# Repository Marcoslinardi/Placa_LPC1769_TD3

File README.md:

# Placa_LPC1769_TD3
Placa de desarrollo para LPC1769

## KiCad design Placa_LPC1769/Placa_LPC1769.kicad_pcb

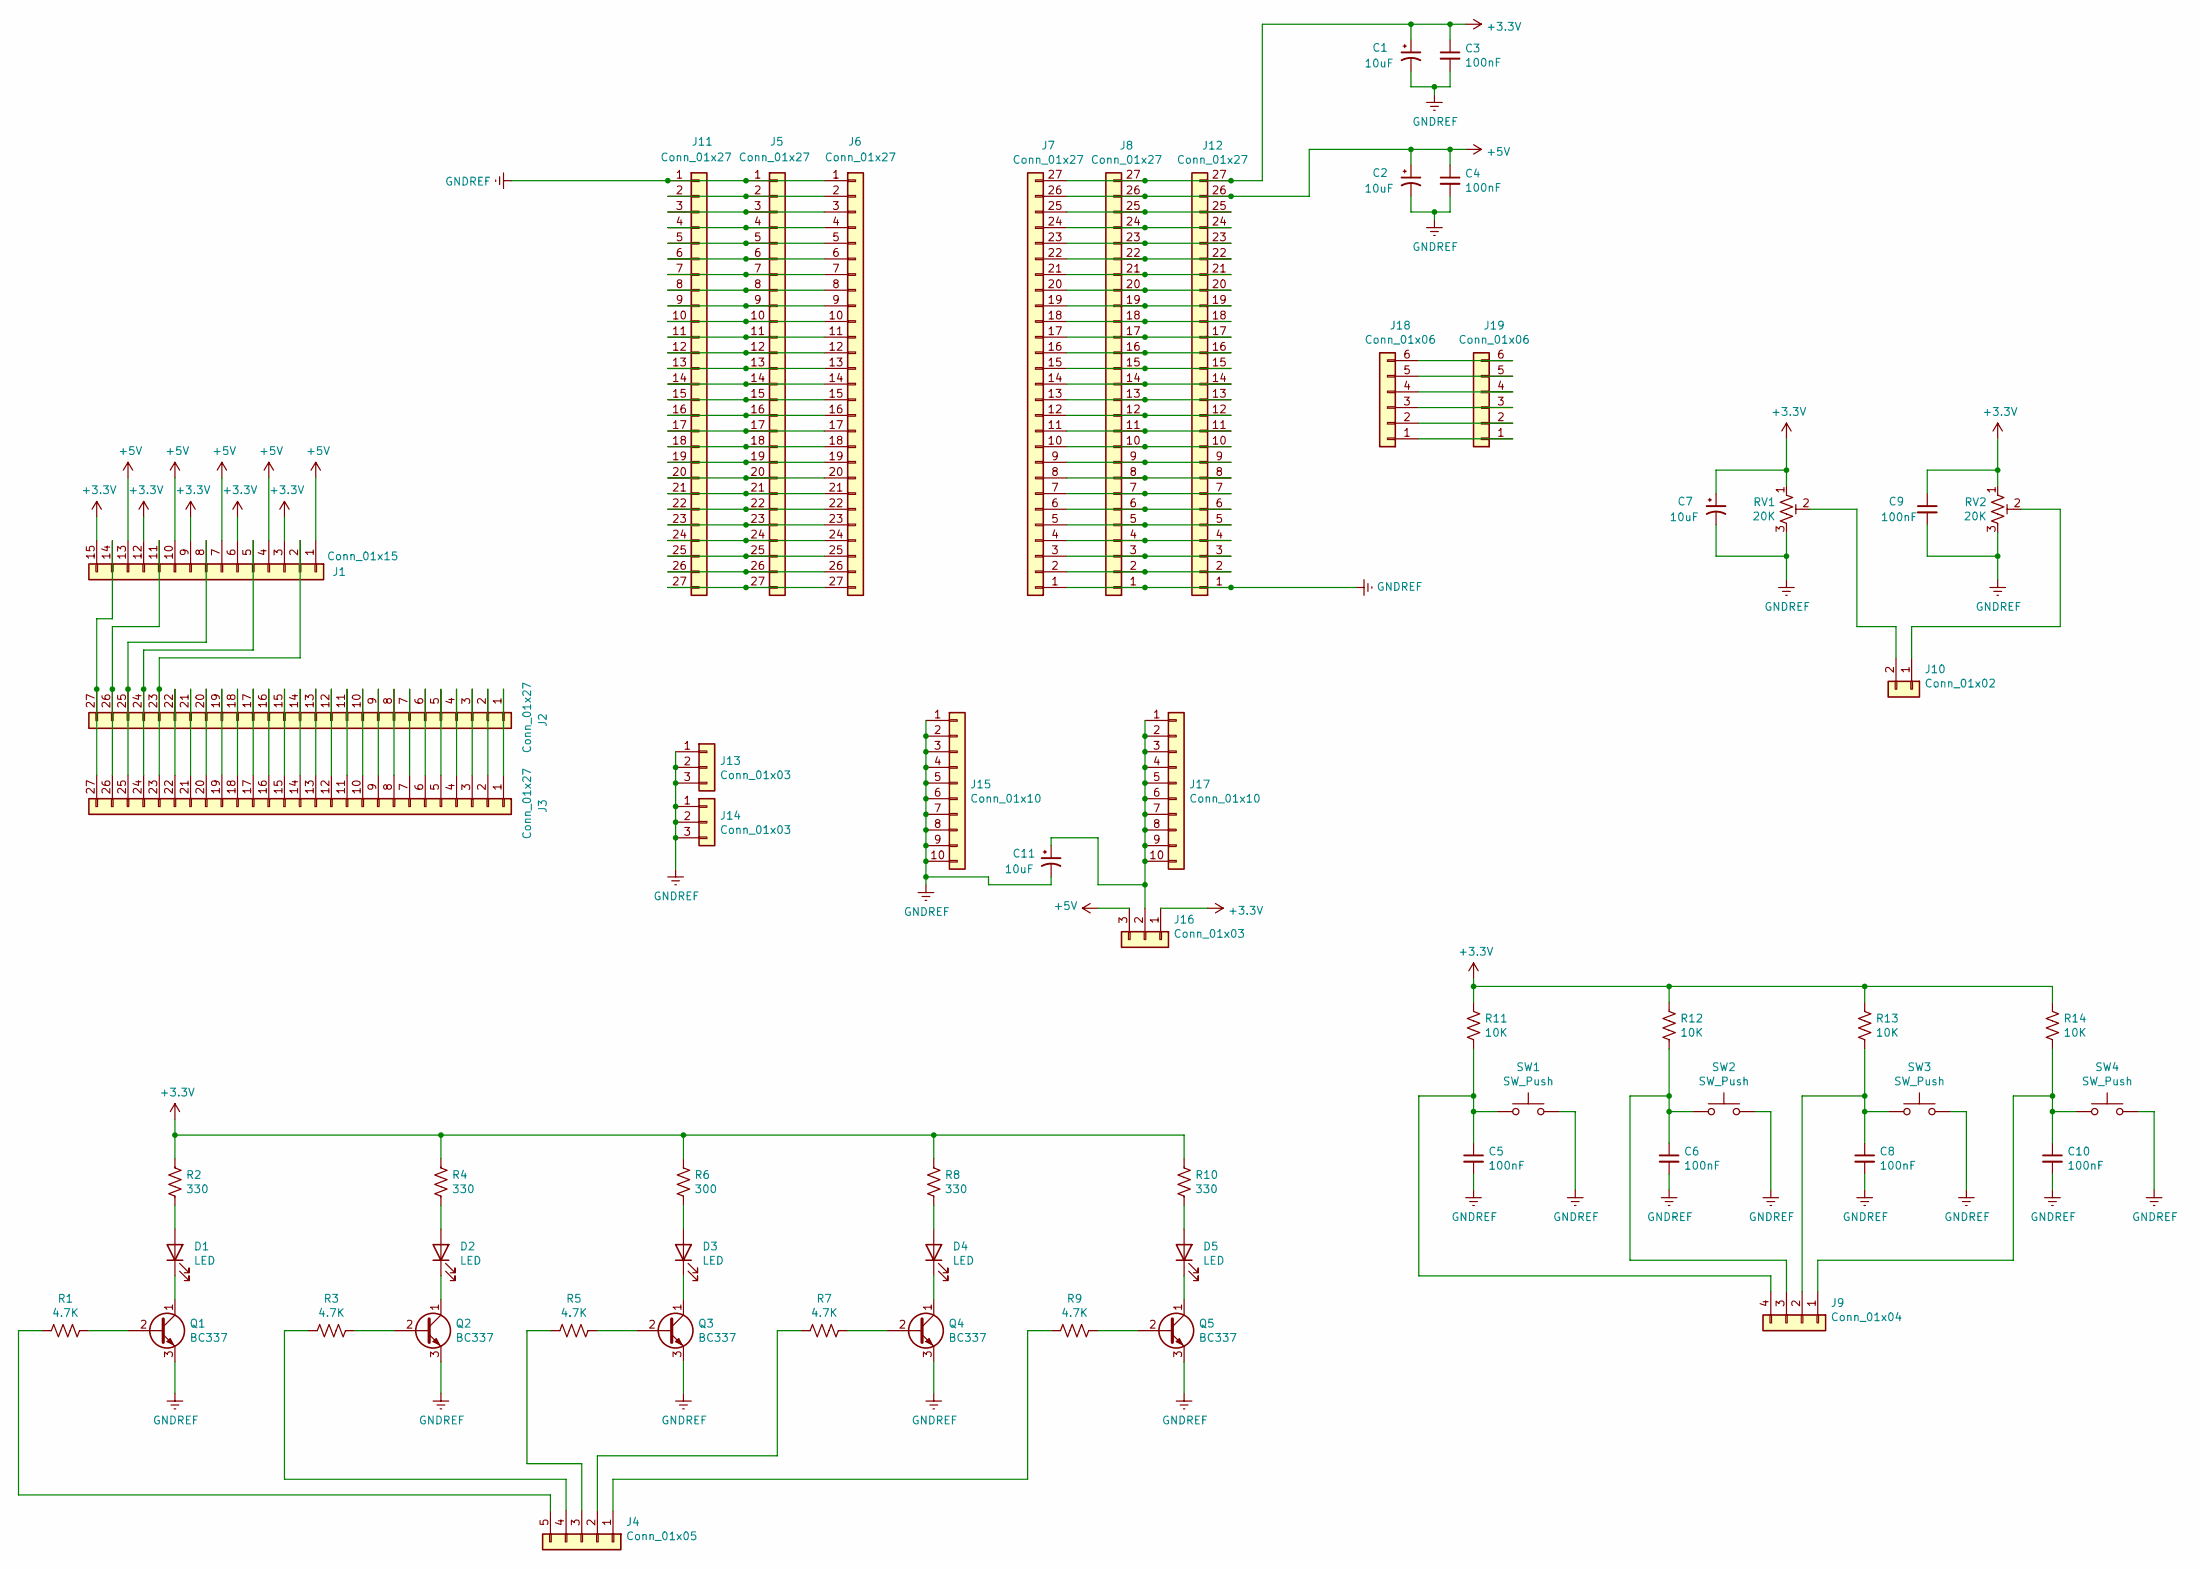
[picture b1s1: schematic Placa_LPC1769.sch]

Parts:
C1, C2, C7, C11: 10uF; CP_Radial_D5.0mm_P2.50mm
C3, C4, C5, C6, C8, C9, C10: 100nF; C_Disc_D5.0mm_W2.5mm_P2.50mm
D1, D2, D3, D4, D5: LED; LED_D3.0mm
J1: Conn_01x15; PinHeader_1x15_P2.54mm_Vertical
J2, J3, J5, J6, J7, J8, J11, J12: Conn_01x27; PinSocket_1x27_P2.54mm_Vertical
J4: Conn_01x05; PinSocket_1x05_P2.54mm_Vertical
J9: Conn_01x04; PinSocket_1x04_P2.54mm_Vertical
J10: Conn_01x02; PinSocket_1x02_P2.54mm_Vertical
J13, J14: Conn_01x03; PinSocket_1x03_P2.54mm_Vertical
J15, J17: Conn_01x10; PinHeader_1x10_P2.54mm_Vertical
J16: Conn_01x03; PinHeader_1x03_P2.54mm_Vertical
J18, J19: Conn_01x06; PinSocket_1x06_P2.54mm_Vertical
Q1, Q2, Q3, Q4, Q5: BC337; TO-92
R1, R3, R5, R7, R9: 4.7K; R_Axial_DIN0309_L9.0mm_D3.2mm_P12.70mm_Horizontal
R2, R4, R8, R10: 330; R_Axial_DIN0309_L9.0mm_D3.2mm_P12.70mm_Horizontal
R6: 300; R_Axial_DIN0309_L9.0mm_D3.2mm_P12.70mm_Horizontal
R11, R12, R13, R14: 10K; R_Axial_DIN0309_L9.0mm_D3.2mm_P12.70mm_Horizontal
RV1, RV2: 20K; Potentiometer_Bourns_3386C_Horizontal
SW1, SW2, SW3, SW4: SW_Push; SW_PUSH_6mm_H5mm

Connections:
+3V3: C1.1, C3.1, C7.1, C9.1, J1.3, J1.6, J1.9, J1.12, J1.15, J7.27, J8.27, J12.27, J16.1, R2.1, R4.1, R6.1, R8.1, R10.1, R11.1, R12.1, R13.1, R14.1, RV1.1, RV2.1
+5V: C2.1, C4.1, J1.1, J1.4, J1.7, J1.10, J1.13, J7.26, J8.26, J12.26, J16.3
GNDREF: C1.2, C2.2, C3.2, C4.2, C5.2, C6.2, C7.2, C8.2, C9.2, C10.2, C11.2, J5.1, J6.1, J7.1, J8.1, J11.1, J12.1, J13.1, J13.2, J13.3, J14.1, J14.2, J14.3, J15.1, J15.2, J15.3, J15.4, J15.5, J15.6, J15.7, J15.8, J15.9, J15.10, Q1.3 (E), Q2.3 (E), Q3.3 (E), Q4.3 (E), Q5.3 (E), RV1.3, RV2.3, SW1.2, SW2.2, SW3.2, SW4.2
unnamed: C5.1, J9.4, R11.2, SW1.1
unnamed: C6.1, J9.3, R12.2, SW2.1
unnamed: C8.1, J9.2, R13.2, SW3.1
unnamed: C10.1, J9.1, R14.2, SW4.1
unnamed: C11.1, J16.2, J17.1, J17.2, J17.3, J17.4, J17.5, J17.6, J17.7, J17.8, J17.9, J17.10
unnamed: D1.1 (K), Q1.1 (C)
unnamed: D1.2 (A), R2.2
unnamed: D2.1 (K), Q2.1 (C)
unnamed: D2.2 (A), R4.2
unnamed: D3.1 (K), Q3.1 (C)
unnamed: D3.2 (A), R6.2
unnamed: D4.1 (K), Q4.1 (C)
unnamed: D4.2 (A), R8.2
unnamed: D5.1 (K), Q5.1 (C)
unnamed: D5.2 (A), R10.2
unnamed: J1.2, J2.23, J3.23
unnamed: J1.5, J2.24, J3.24
unnamed: J1.8, J2.25, J3.25
unnamed: J1.11, J2.26, J3.26
unnamed: J1.14, J2.27, J3.27
unnamed: J2.1, J3.1
unnamed: J2.2, J3.2
unnamed: J2.3, J3.3
unnamed: J2.4, J3.4
unnamed: J2.5, J3.5
unnamed: J2.6, J3.6
unnamed: J2.7, J3.7
unnamed: J2.8, J3.8
unnamed: J2.9, J3.9
unnamed: J2.10, J3.10
unnamed: J2.11, J3.11
unnamed: J2.12, J3.12
unnamed: J2.13, J3.13
unnamed: J2.14, J3.14
unnamed: J2.15, J3.15
unnamed: J2.16, J3.16
unnamed: J2.17, J3.17
unnamed: J2.18, J3.18
unnamed: J2.19, J3.19
unnamed: J2.20, J3.20
unnamed: J2.21, J3.21
unnamed: J2.22, J3.22
unnamed: J4.1, R9.2
unnamed: J4.2, R7.2
unnamed: J4.3, R5.2
unnamed: J4.4, R3.2
unnamed: J4.5, R1.2
unnamed: J10.1, RV2.2
unnamed: J10.2, RV1.2
unnamed: J5.2, J6.2, J11.2
unnamed: J5.3, J6.3, J11.3
unnamed: J5.4, J6.4, J11.4
unnamed: J5.5, J6.5, J11.5
unnamed: J5.6, J6.6, J11.6
unnamed: J5.7, J6.7, J11.7
unnamed: J5.8, J6.8, J11.8
unnamed: J5.9, J6.9, J11.9
unnamed: J5.10, J6.10, J11.10
unnamed: J5.11, J6.11, J11.11
unnamed: J5.12, J6.12, J11.12
unnamed: J5.13, J6.13, J11.13
unnamed: J5.14, J6.14, J11.14
unnamed: J5.15, J6.15, J11.15
unnamed: J5.16, J6.16, J11.16
unnamed: J5.17, J6.17, J11.17
unnamed: J5.18, J6.18, J11.18
unnamed: J5.19, J6.19, J11.19
unnamed: J5.20, J6.20, J11.20
unnamed: J5.21, J6.21, J11.21
unnamed: J5.22, J6.22, J11.22
unnamed: J5.23, J6.23, J11.23
unnamed: J5.24, J6.24, J11.24
unnamed: J5.25, J6.25, J11.25
unnamed: J5.26, J6.26, J11.26
unnamed: J5.27, J6.27, J11.27
unnamed: J7.2, J8.2, J12.2
unnamed: J7.3, J8.3, J12.3
unnamed: J7.4, J8.4, J12.4
unnamed: J7.5, J8.5, J12.5
unnamed: J7.6, J8.6, J12.6
unnamed: J7.7, J8.7, J12.7
unnamed: J7.8, J8.8, J12.8
unnamed: J7.9, J8.9, J12.9
unnamed: J7.10, J8.10, J12.10
unnamed: J7.11, J8.11, J12.11
unnamed: J7.12, J8.12, J12.12
unnamed: J7.13, J8.13, J12.13
unnamed: J7.14, J8.14, J12.14
unnamed: J7.15, J8.15, J12.15
unnamed: J7.16, J8.16, J12.16
unnamed: J7.17, J8.17, J12.17
unnamed: J7.18, J8.18, J12.18
unnamed: J7.19, J8.19, J12.19
unnamed: J7.20, J8.20, J12.20
unnamed: J7.21, J8.21, J12.21
unnamed: J7.22, J8.22, J12.22
unnamed: J7.23, J8.23, J12.23
unnamed: J7.24, J8.24, J12.24
unnamed: J7.25, J8.25, J12.25
unnamed: J18.1, J19.1
unnamed: J18.2, J19.2
unnamed: J18.3, J19.3
unnamed: J18.4, J19.4
unnamed: J18.5, J19.5
unnamed: J18.6, J19.6
unnamed: Q1.2 (B), R1.1
unnamed: Q2.2 (B), R3.1
unnamed: Q3.2 (B), R5.1
unnamed: Q4.2 (B), R7.1
unnamed: Q5.2 (B), R9.1

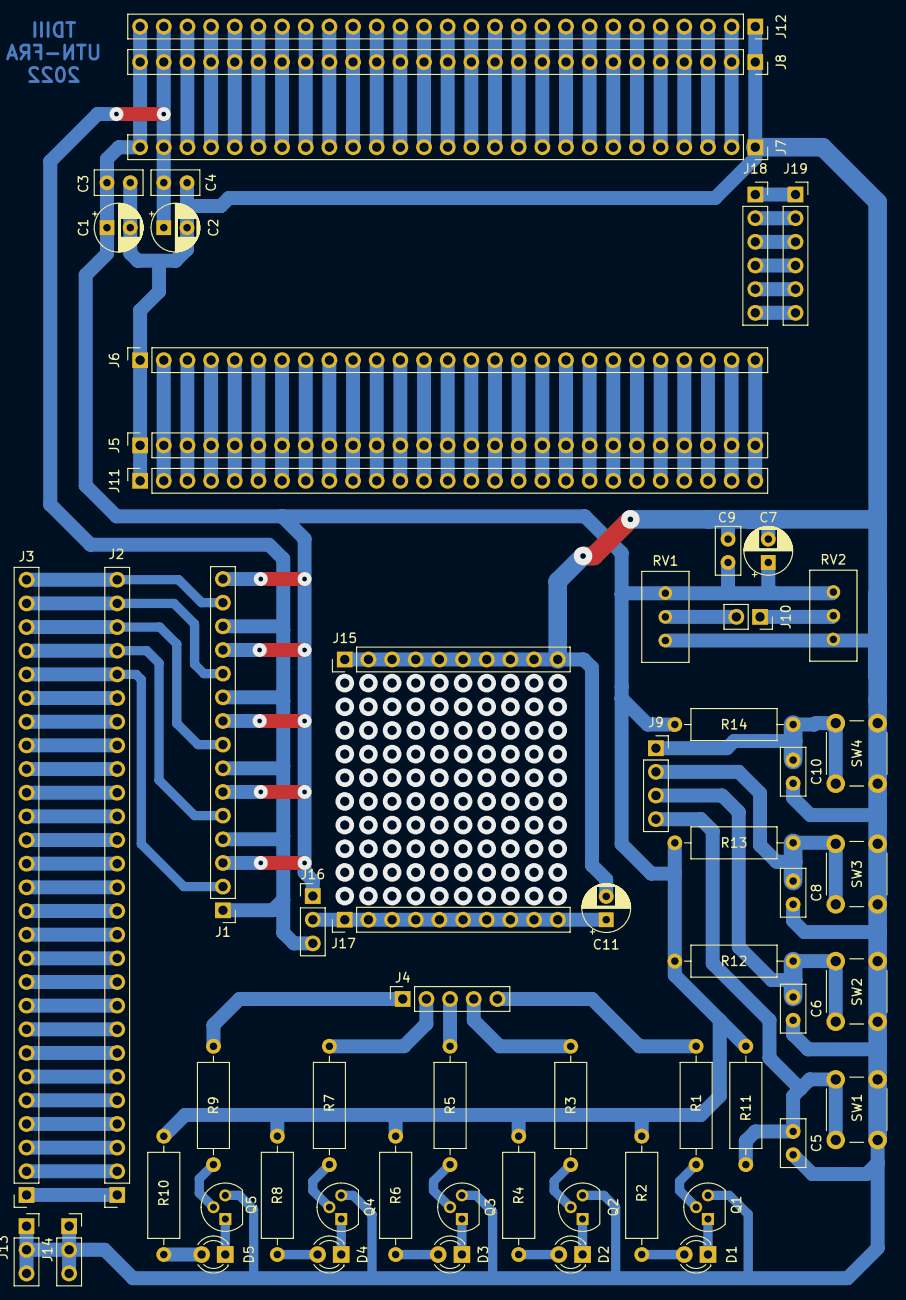
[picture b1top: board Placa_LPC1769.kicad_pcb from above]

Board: 2 copper layers, 60 parts (0 on the bottom side), 113 nets.

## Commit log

2022-05-22 Subo Esquematico + PCB
